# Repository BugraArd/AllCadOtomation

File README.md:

# AllCadOtomation — pcbqa

KiCad üzerinde çalışan bir **devre tasarımı otomasyonu ve kalite denetimi**
aracı. Saf Python'dur (çalışma zamanı bağımlılığı yok) ve KiCad'in kendi
Python'uyla çalışır.

Yaptıkları:

- **Analiz:** `.kicad_sch` + `.kicad_pcb` okunur, kaynaklı kural kütüphanesiyle
  (IPC-2221B, üretici uygulama notları) denetlenir ve skorlanır.
- **Devre grafı:** her parçanın pinleri, devredeki rolü, güç/gerilim sınırları,
  PCB karşılığı ve **eksik bilgileri** tek modelde toplanır.
- **Üç seviyeli doğrulama:**
  1. KiCad ERC / DRC / şematik paritesi
  2. parçaya ve amaca bağlı mühendislik kuralları
  3. **ngspice** benzetimi (tolerans, sıcaklık, yaşlanma)
- **PCB:** önce yerleşim ve kısıtlar, sonra dal akımına göre iz genişliği.
  Kirchhoff çözümüyle her iz parçasının gerçek akımı, darboğazlar, vialar ve
  gerilim düşümü hesaplanır.
- **Üretken tasarım:** niyet YAML'ından şematik + kart üretimi, otomatik
  yerleştirme, varyant keşfi (önce STM32).
- **KiCad'e bağlanma:** dosya, `pcbnew` (SWIG) ya da IPC. Açık PCB'de canlı
  düzenleme tek Ctrl+Z ile geri alınabilir.
- **ML veri hattı:** doğrulama ve yerleştirme sonuçları veri kümesine yazılır.

## Gereksinimler

| | Sürüm |
|---|---|
| KiCad | **10.0.4** (kicad-cli, sembol/footprint kütüphaneleri, `ngspice.dll`) |
| KiCad'in Python'u | 3.11.5 — dağıtımda bunu kullanır (`pcbqa.cmd`) |
| Geliştirme | Python 3.13 + `pcbqa/.venv` (`pyyaml`, `kicad-python`) |
| Benzetim | ngspice-46 (KiCad ile gelir; ek kurulum gerekmez) |
| İsteğe bağlı | KiCad nightly 10.99 (yalnızca canlı şematik için, `pcbqa/.runtime/`) |

## Hızlı başlangıç

```bat
cd pcbqa
pcbqa tani                                     :: ortam denetimi
pcbqa analiz samples\pic_programmer            :: kalite raporu
pcbqa devre  <proje>                           :: devre grafı ve eksikler
pcbqa dogrula <proje> --kosullar k.yaml        :: ERC/DRC + mühendislik + ngspice + PCB + 9 kontrol
pcbqa kontrol <proje> --kosullar k.yaml        :: hepsi tek koşuda: kalite skoru + doğrulama (ERC/DRC bir kez)
pcbqa uret --intent samples\niyetler\g031-asgari.yaml --out cikti\g031
pcbqa arayuz                                   :: masaüstü arayüzü (Yap, Devre, Kontrol, Düzelt, Deney, Üret, Canlı)
```

Kurulum ayrıntısı: `docs/KURULUM.md`. Tüm komutlar: `pcbqa --help`.

## Klasör yapısı

```
Kicad/
├─ pcbqa/                  uygulama
│  ├─ pcbqa/               Python paketi
│  │  ├─ app.py            tek giriş noktası (alt komutlar)
│  │  ├─ devre/            ortak devre modeli (graf, parça bilgisi, roller, koşullar)
│  │  ├─ dogrulama/        seviye 1-2-3 + dokuz kontrol
│  │  ├─ spice/            ngspice entegrasyonu
│  │  ├─ pcb_akim.py       dal akımı ve yönlendirme girdisi
│  │  ├─ rules.py, ipc2221.py, thermal.py, circuit.py   kural motoru ve hesaplar
│  │  ├─ placement/        yerleştiriciler (auto = üretim)
│  │  ├─ sch_*.py, pcb_sync.py   şematik/kart yazma (netlist kalkanıyla)
│  │  ├─ intent.py, generate.py, explore.py, templates/   üretken tasarım
│  │  ├─ canli*.py, ipc*.py, swig_apply.py   KiCad bağlantısı
│  │  ├─ data/parcalar/    kaynaklı parça bilgi kütüphanesi
│  │  └─ ml/               veri kümesi ve modeller
│  ├─ tests/               1035 unittest
│  └─ samples/             örnek projeler ve niyetler
├─ docs/                   TÜM belgeler: HANDOFF, KURULUM, tasarım kuralları,
│                          yol haritası, devre modeli, hafiza/ (Beads'ten üretilir), paketler/
├─ graphify-out/           bilgi grafiği
├─ .beads/                 iş takibi ve kalıcı hafıza (Beads)
├─ AGENTS.md               yapay zekâ ajanları için tek dosya (kurallar + yapı + hafıza)
└─ CLAUDE.md               AGENTS.md'yi içe aktarır
```

Özelliklerin tam haritası (hangi komut hangi modülde, ne yapar) `AGENTS.md`
bölüm 4'te.

## Testler

```bat
cd pcbqa
.venv\Scripts\python.exe -m unittest discover -s tests          :: 1035 test, ~5 dk
.venv\Scripts\python.exe -m unittest discover -s tests -p "test_spice.py"
```

Son koşu 2026-10-01'de yapıldı: 1035 test, hepsi geçti. Dosya bazında liste
`AGENTS.md` bölüm 6'da.

## Belgeler

| Belge | İçerik |
|---|---|
| `pcbqa/README.md` | Uygulamanın ayrıntılı kullanımı |
| `docs/HAFIZA-HARITASI.md` | Tüm hafıza, ayar ve belge dosyaları: nerede, neden orada |
| `docs/KURULUM.md` | Kurulum, kısayol, canlı mod |
| `docs/HANDOFF.md` | Tam geliştirme bağlamı ve ölçülmüş kararlar |
| `docs/devre-modeli-ve-dogrulama.md` | Devre grafı, 3 seviyeli doğrulama, PCB dal akımı |
| `docs/tasarim-kurallari/` | Kural eşiklerinin kaynakları |
| `docs/yol-haritasi-skorlama.md` | Yol haritası |
| `docs/duzeltme-siralama.md` | ML ilk deneyi: düzeltme adayı sıralama, sonuçlar ve eksikler |

## Proje hafızası

İşler ve kalıcı kararlar **Beads**'te tutulur (`bd ready`, `bd recall <anahtar>`).
Kod ve belge ilişkileri **graphify** bilgi grafiğinde sorgulanır
(`graphify explain "<kavram>"`). Serena kullanılmaz.

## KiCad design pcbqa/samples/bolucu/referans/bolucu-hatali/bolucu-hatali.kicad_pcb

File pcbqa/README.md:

# pcbqa — KiCad tasarım kalite analizi ve otomatik yerleştirme

KiCad projelerini **salt-okunur** analiz eden bir araç. Tasarımınızda hiçbir
değişiklik yapmaz — sadece okur, ölçer ve rapor eder.

## Ne yapar?

KiCad şematiği ile PCB'yi ayrı ayrı bilir ama **ikisini birleştirmez**. ERC size
"bu pin bağlı değil" der; "bu decoupling kondansatörü 33 mm ötede" demez.
`pcbqa` tam olarak o boşluğu doldurur:

```
U2.VCC_14 için en yakın C1 33.3 mm uzakta (hedef <= 20 mm), net VCC
```

Üç kaynağı tek raporda birleştirir:

| Kaynak | Ne verir |
|---|---|
| `kicad-cli sch export netlist` | Hangi pin hangi nette, pin işlevleri ve tipleri |
| `.kicad_pcb` | Bileşenlerin ve pad'lerin fiziksel konumu, courtyard, kart sınırı |
| `kicad-cli sch erc` / `pcb drc` | KiCad'in kendi kontrolleri |

**Şematik zorunlu değil.** KiCad 9+ pad'lerde hem net adını hem pin tipini
sakladığı için kuralların neredeyse tamamı sadece `.kicad_pcb` ile çalışır.
Şematik varsa ek olarak pin işlev adları (`VCC_8`) ve net sınıfları gelir.

## Kurulum

Gereksinim: KiCad 9 veya üzeri (`kicad-cli` için) ve Python 3.10+.
IPC ile çalışan KiCad'e placement yazmak için ayrıca `kicad-python` kurulur.

```powershell
cd C:\Users\ardaa\OneDrive\Desktop\Kicad\pcbqa
python -m venv .venv
.\.venv\Scripts\python -m pip install -r requirements.txt
```

`kicad-cli` otomatik bulunur (PATH → `C:\Program Files\KiCad\*\bin`). Gerekirse:

```powershell
$env:PCBQA_KICAD_CLI = "C:\Program Files\KiCad\10.0\bin\kicad-cli.exe"
```

## Kullanım

```powershell
# Demo proje üzerinde
.\.venv\Scripts\python -m pcbqa samples\pic_programmer

# Kendi projeniz + kendi kurallarınız + JSON çıktı
.\.venv\Scripts\python -m pcbqa C:\yol\projem --rules rules.yaml --json rapor.json

# Bulguları kimlikleri ve kanıtlarıyla listele
pcbqa duzelt C:\yol\projem --liste

# Bir bulguyu doğrudan düzelt (planı yazar ve aynı koşumda uygular)
pcbqa duzelt C:\yol\projem --finding F-123456789abc

# İlk STM32G0 profilinden geçici KiCad projesi üret
pcbqa uret --intent samples\niyetler\g031-asgari.yaml --out C:\yol\g031-kart

# BOM'da yalnızca kaynağı doğrulanmış kalemleri üretime kabul et
pcbqa bom samples\bom\g031-asgari.yaml --fail-on-open
```

Ya da kısayol: `run.cmd samples\pic_programmer`

### Var olan sembolleri telleme (`bagla`)

```powershell
# Sayfaya baksın ve gerekçesiyle önersin (yazmaz)
.\.venv\Scripts\python -m pcbqa.connect samples\uc_parca\uc_parca.kicad_sch --oner

# Öneriyi çiz
.\.venv\Scripts\python -m pcbqa.connect samples\uc_parca\uc_parca.kicad_sch --oner --uygula

# Ya da hangi pinlerin aynı ağa gireceğini kendiniz söyleyin
.\.venv\Scripts\python -m pcbqa.connect <şematik> --ag "#PWR01.1 R1.1 C1.1" --uygula
```

`--oner` niyeti **yerleşimden** okur: iki boş pin birbirinin en yakın hizalı
komşusuysa ve aralarında engel yoksa bağlanır; güç sembolü bir rayın ortasına
dik iniyorsa oraya iner. Kanıtı olmayan hiçbir şey önerilmez ve **atlanan pin
adıyla söylenir**. Aynı sembolün kendi pinleri asla eşleşmez — o hizalama
sembolün geometrisinden gelir, kullanıcının yerleşiminden değil.

Yazdıktan sonra `kicad-cli` netlist'i hakemdir: istenen pinler gerçekten aynı
ağa girmediyse komut hata döner ve yedeğin yolunu söyler.

### Bulgu / düzeltme / doğrulama

`duzelt` komutu analiz bulgularına kararlı `Finding ID`, ölçüm ve kanıt özeti
verir. Paket 01'de yalnızca ölçülmüş decoupling mesafesi ihlalleri otomatik
düzeltme adayıdır.

`--finding` verilen komut **ayrı bir onay adımı beklemez** (kullanıcı talimatı,
2026-09-27): planı ekrana yazar ve aynı koşumda uygular. Güvenlik önizlemeden
değil yazma kapılarından gelir ve hepsi korunur — uygulama öncesi yedek alınır,
KiCad açıkken yazma reddedilir, sonrasında hedef bulgu ile netlist paritesi
tekrar kontrol edilir ve doğrulama başarısızsa dosya yedekten geri alınır.
Mevcut track/via/zone bulunan yönlendirilmiş kartlar otomatik dosya
uygulamasına hâlâ alınmaz.

### STM32G0 ilk profil

Paket 02’nin ilk dikey dilimi `mcu-stm32g031k8` şablonudur. Hedef parça
`STM32G031K8T6`, paket `LQFP-32_7x7mm_P0.8mm`’dir. Profil; güç, reset ve
temel SWD bağlantısını üretir. LQFP-32 varyantında USB ve HSE varsayılmaz;
PA14’ün SWCLK/BOOT0 çoklaması nedeniyle BOOT0 pulldown otomatik eklenmez.
Gerçek ürün BOM’u ve çevresel pin seçimi elektriksel gereksinim onayından
sonra kilitlenecektir.

### BOM kaynak kapısı

`pcbqa bom` fiyat veya stok uydurmaz. Her kalem `verified`, `needs_selection`,
`blocked` veya `synthetic` olarak görünür. `verified` kalemlerde MPN, üretici
ve kaynak zorunludur; `--fail-on-open` açık kalem varsa çıkış kodu `1` döndürür.

## Aşama 5: makine öğrenimi altyapısı

Aşama 3'ün dersi "yerleştirici, hakemin puanladığı şeyi optimize etmeli"ydi.
Aşama 5 sıradaki soruyu sorar: hakemin ölçümü **doğru ama pahalı** (60
bileşenli kartta 2 ms, `pic_programmer`da 6 ms, `jetson` gibi kartlarda çok
daha fazla — `auto`nun süre bütçesini aşmasının sebebi bu). Yerel arama saniyede
binlerce aday dener; bunların hangisinin denemeye değer olduğunu **öğrenilmiş
bir model** söyleyebilir mi?

```powershell
# 1) Gerçek hakemle etiketlenmiş veri topla
.\.venv\Scripts\python -m pcbqa.ml.collect --suite "C:\Program Files\KiCad\10.0\share\kicad\demos" `
    --board samples\bench_bad.kicad_pcb --rules pcbqa\default_rules.yaml `
    --out .work\moves.jsonl --budget 25

# 2) Modelleri eğit ve KARŞILAŞTIR (mean = taban çizgisi, identity'nin ML karşılığı)
.\.venv\Scripts\python -m pcbqa.ml.train .work\moves.jsonl --model all --target all --cv 5 `
    --out pcbqa\ml\models\move-v1.json

# 3) Öğrenilmiş sıralamayla yerleştir
.\.venv\Scripts\python -m pcbqa.harness --placer auto --placer learned --board samples\bench_bad.kicad_pcb
```

### Model karar vermez, sıra önerir

Bu ayrım altyapının tamamını belirledi. Model yalnızca aday hamleleri
**denenme sırasına** dizer; bir hamlenin kabul edilip edilmeyeceğine hâlâ
`ctx.evaluate` (gerçek hakem) karar verir. Sonuçları:

- Model iyi çalışırsa aynı bütçede daha çok iyileşme yakalanır.
- Model **tamamen yanılırsa** sonuç sadece biraz yavaşlar; skor düşemez.
- Bozuk/eski bir model dosyası aramayı durduramaz — sıralayıcı patlarsa
  arama kendi sırasıyla devam eder.

Testlerde bu bilerek zorlanıyor: kasten **en kötü hamleyi başa alan** bir
sıralayıcıyla ve her çağrıda istisna fırlatan bir sıralayıcıyla `polish`
koşturuluyor; ikisinde de sonuç başlangıçtan kötü çıkmıyor.

### Ölçülen şey: kaç değerlendirmede ilk iyileşmeyi buluyoruz

R² değil. Yerel arama ilk iyileştiren hamleyi kabul ettiği için asıl soru
"skoru artıran hamleye kaçıncı denemede ulaşıldığı". Taban, cilanın **bugün**
kullandığı sıra. 21 karttan toplanan 49.699 örnekte, kart bazlı 5 katlı çapraz
doğrulama:

| model | hedef | ikili doğruluk | skor hızlanması |
|---|---|---|---|
| mean (taban) | — | 0.500 | 1.00x |
| ridge | sign | **0.714** | **1.56x** |
| gbt | score | 0.581 | 1.53x |
| ridge | score | 0.691 | 1.51x |
| gbt | value | 0.698 | 1.36x |
| ridge | value | 0.695 | 1.34x |

Yani öğrenilecek gerçek bir sinyal var: model, skoru artıran hamleyi ortalama
2.8 yerine ~1.4 denemede buluyor.

### Uçtan uca sonuç: `learned` şu an `auto`yu geçmiyor

Dürüst tablo şu: sıralama kazancı yerleştirme **kalitesine** yansımıyor.
Modelin hiç görmediği dört kartta (eğitim kümesinden çıkarılarak), 5 sn bütçe:

| kart | önce | `auto` | `learned` |
|---|---|---|---|
| pic_programmer | 45 | 94 | 94 |
| complex_hierarchy | 54 | 94 | 94 |
| sonde xilinx | 73 | 100 | 100 |
| interf_u | 5 | 12–14 | 12–15 |
| jetson (1125 bileşen, 60 sn) | 93 | 93.3 | 93.3 |

`interf_u` satırındaki oynama üç tekrarda `auto` için de aynı aralıkta çıkıyor
— duvar saati bütçesinden gelen gürültü, model etkisi değil. Sebep basit:
bu bütçelerde `auto` zaten doyuma ulaşıyor, sıralamayı hızlandırmak
ulaşılabilir tavanı yükseltmiyor. `learned` bu yüzden `force`/`anneal` gibi bir
**araştırma yerleştiricisi** olarak duruyor; üretim yerleştiricisi hâlâ `auto`.

### Yol boyunca bulunan iki gerçek problem

**1. Etiket seçimi model seçiminden daha önemli.** İlk model `sign` hedefiyle
(“hakemi mutlu eder mi”) eğitildi ve `complex_hierarchy`yi 94 → 81 **düşürdü**
— üstelik HPWL'i iyileştirerek (1680 → 1594). Sebep veri kümesinde görünüyor:
etiketi pozitif olan hamlelerin **%81'i skoru hiç değiştirmiyor**, yalnızca
teli birkaç mm kısaltıyor. Model bunları öğrenip cilayı mikro HPWL
kazançlarına yönlendirdi, hakemin saydığı hatalar açık kaldı. Kural: modele
neyi sıralamasını istiyorsak etiket **tam olarak o** olmalı (`--target score`).

**2. Her sıra bilgisiz değildir.** Onarım aşamasında hamleler zaten anlamlı bir
sırada üretiliyor: yarıçap artan, yani "en küçük yer değiştirme önce". Bu
muhafazakâr sıra komşu kısıtları bozmadığı için değerlidir; modelin "tek başına
en çok iyileştiren" hamlesi ise büyük sıçramalar seçip başka bulguları
açıyordu. Sıralayıcı bu yüzden **yalnızca ince ayar aşamasında** devreye
giriyor — orada sıra bugün zaten `rng.shuffle` ile rastgele, yani kaybedilecek
bilgi yok. Bu kısıtlamadan sonra dört model varyantının hiçbiri gerileme
yapmadı.

### Öznitelikler neden yerel

75 öznitelik var (şema v3) ve hepsi tek bir bileşenin **kendi netleri ve yakın
komşularıyla** hesaplanıyor; maliyet kartın büyüklüğüne değil bileşenin
derecesine bağlı. Ölçüldü:

| kart | bileşen | öznitelik | tam değerlendirme | oran |
|---|---|---|---|---|
| bench_bad | 18 | 32 µs | 2.09 ms | 65x |
| pic_programmer | 63 | 72 µs (v1) · 134 µs (v3) | 6.12 ms | 85x · 45x |

Şema v3 bulgunun **kendisini** de taşıyor: kural tipi, `(ölçülen − limit)/limit`
boşluğu ve — `proximity` için — hamleden sonraki ölçümün **birebir yeniden
hesabı**. `proximity` pin-pin mesafesi ölçtüğü için bileşen merkezi yaklaşımı
tam da kuralın karar verdiği eşiğin çevresinde yanılıyordu (SOIC-20'de bir pin
merkeze 5 mm uzakta olabilir). Ayrıntı: HANDOFF §14.

Yerel hesabın sessizce yanlış olmaması kritik — model o zaman sağlam veriyle
eğitildiğini sanır. Bu yüzden `d_hpwl` özniteliği testlerde **tam yeniden
hesaplamayla** karşılaştırılıyor.

### Bağımlılık yok

`numpy`/`scikit-learn` eklenmedi. Ridge regresyon (normal denklemler +
Cholesky) ve gradyan artırmalı ağaçlar (histogram tabanlı) saf Python;
problem boyutu (~50 öznitelik, ~50 bin satır) bunun için fazlasıyla küçük ve
proje `sexpr.py`den beri bağımlılıksız kalmayı tercih ediyor. Modeller
**JSON** olarak saklanıyor: git diff'i okunabilir, Python sürümleri arasında
taşınabilir, ve içinde çalıştırılabilir kod olmadığı için başkasından gelen bir
model dosyasını açmak güvenlik sorunu değil.

## Aşama 4a/4b: şematik okuma ve netlist kalkanı

KiCad 10'da IPC API'si yalnızca PCB editöründe var. Ama şematiği **okumak**
için IPC'ye gerek yok: `.kicad_sch` da s-expression. `pcbqa.schematic` onu
doğrudan okur — hiyerarşik alt sayfalar dahil.

```python
from pcbqa.schematic import read_schematic

sch = read_schematic("proje/proje.kicad_sch")   # alt sayfalara kendi iner
sch.stats()          # {'dosya': 2, 'sayfa': 2, 'sembol': 124, ...}
r1 = sch.by_ref("R1")
r1.pins              # sayfa koordinatına çözülmüş pinler
r1.bbox              # gövde sınır kutusu
```

Analiz raporuna `SEMATIK` bölümü olarak da yansır (`python -m pcbqa <proje>`)
ve dört yapısal kontrol ekler: eksik alt sayfa dosyası, ızgara dışı sembol,
footprint'i atanmamış bileşen, gövdeleri çakışan semboller.

### Pin konumu: deneysel olarak doğrulanmış dönüşüm

Kütüphane sembolünde Y **yukarı**, sayfada Y **aşağı** bakar; sembol ayrıca
döndürülmüş ve aynalanmış olabilir. Doğru dönüşüm tahminle değil, KiCad'in 19
demo projesinin tamamında ölçülerek seçildi:

| | örtüşme |
|---|---|
| `(px·cos − py·sin, −px·sin − py·cos)` | **%93.5** |
| rakip hipotez | %37.8 |
| ayna **rotasyondan sonra** | **%94.9** |
| ayna rotasyondan önce | %27.0 |

Okuyucu 19 projede, **17.088 pin** üzerinde doğrulandı: pinlerin **%98.7'si**
bir çapaya oturuyor, projelerin çoğunda %100, bozuk parantez 0.

> Çapa yalnızca tel ucu değildir. Bir pin junction'a, no-connect'e, etikete
> veya **doğrudan başka bir sembolün pinine** de değebilir — güç sembolleri
> (GND, VCC) çoğu zaman telsiz, doğrudan IC pinine yapışır. Dar bir ölçüt
> bunları "kaçan pin" sanar.

### Netlist değişmezliği kalkanı

Şematikte bağlantı **geometriktir**: tel ucu pine değiyorsa bağlıdır. PCB'de
durum farklı — orada net, pad'in içinde ismiyle yazılıdır. Sonuç: bir sembolü
şematikte kaydırmak bağlantıyı **sessizce** koparır.

Ölçüldü: `pic_programmer` üzerinde R1 kaydırıldığında pin 2 koptu ve netlist'te
`unconnected-(R1-Pad2)` olarak belirdi. Hiçbir hata, hiçbir uyarı. **Tek ızgara
adımı (1.27 mm) bile yetiyor.**

```python
from pcbqa.sch_verify import verify_unchanged

diff = verify_unchanged(onceki_sch, sonraki_sch)
if not diff.ok:
    print(diff.describe())    # "BAGLANTI DEGISTI: 7 pin baska aga tasindi"
    for satir in diff.details():
        print(satir)
```

Doğru değişmez, ham XML değil **pinlerin ağlara bölünüşüdür**. Net kodları her
ihracatta yeniden numaralanır ve otomatik net adları (`Net-(R1-Pad1)`)
konuma göre değişir; bunlar gerçek bağlantı değişikliği değildir. Bölünme aynı
kaldığı sürece devre elektriksel olarak aynıdır.

Bu kalkan, şematiğe yazma (Aşama 4c/4d) için ön koşuldur: yazma öncesi/sonrası
karşılaştırılır, `ok=False` ise yazma reddedilir.

## Aşama 4e: şematik yerleştirme kalitesi

Aşama 3'te PCB için kurulan mimari şematiğe olduğu gibi taşındı: yerleştirici
vekil bir maliyet uydurmaz, **hakemin gerçek ölçütünü** optimize eder ve sonuç
hiçbir zaman başlangıçtan kötü olamaz. `refine.polish` değiştirilmeden
kullanılır; değişen tek şey değerlendiricidir.

```powershell
# Bir sayfayı iyileştir (dry-run), sonra uygula
.\.venv\Scripts\python -m pcbqa.sch_apply --sch proje\proje.kicad_sch --budget 20
.\.venv\Scripts\python -m pcbqa.sch_apply --sch proje\proje.kicad_sch --budget 20 --apply

# Alt sayfa
.\.venv\Scripts\python -m pcbqa.sch_apply --sch proje\proje.kicad_sch --sheet /guc --apply
```

### İki hızlı, bir yavaş ölçüt

Kalkan her çağrıda `kicad-cli` çalıştırır (2-4 sn); yerel arama binlerce aday
dener. Bu yüzden ölçüt ikiye ayrıldı:

| | ne zaman | ne kadar sürer |
|---|---|---|
| Geometrik ölçüt (bellek-içi) | her adayda | **~0.4 ms** → 20 sn'de ~47.000 deneme |
| Netlist kalkanı | yalnızca yazmadan önce, **bir kez** | 2-4 sn |

Geometrik ölçüt bağlantı riskini de taşır: taşınan bir pin **kendisine ait
olmayan** bir çapaya (başka bir telin ucu, başka bir sembolün pini) oturursa
iki net birleşir. Bu, kalkanın yakaladığı hatanın ucuz vekili olduğu için arama
zaten oraya gitmez; kalkan son söz olarak kalır.

Ölçülen: `pic_programmer` kök sayfası 985.5 → 976.6 mm, skor 100'de sabit,
0 hata. Daha dağınık sayfalarda kazanç çok daha büyük (`video/RAMS` %21,
`vme-wren` kök sayfası %17).

### Bus içeren sayfalar: varsayılan olarak kapalı

Ucuz ölçüt bus bağlantılarını modelleyemiyor. `vme-wren/vme_p1_p2` sayfasında
(137 bus, 262 bus girişi) optimizasyon "skor 100, 0 hata, tel %60 kısaldı"
dedi; gerçek kalkan **257 pinin ağ değiştirdiğini** gösterdi ve yazma
reddedildi. Sistem güvenliydi ama ölçüm yanıltıcıydı.

Bu yüzden bus içeren sayfalarda optimizasyon kapalıdır. `allow_buses=True`
ile açılabilir — kalkan yine son söz olarak çalışır.

### Toplu uygulama

`sch_move` tek sembol taşır ve her çağrıda kalkanı çalıştırır — 30 sembol için
dakikalar. `sch_apply` tersini yapar: **tüm** taşımaları ağaç üzerinde uygular,
kalkanı **bir kez** çalıştırır, dosyayı **bir kez** yazar.

Bir nokta iki taşınan sembolün pinine denk gelip deltaları farklıysa, o noktayı
nereye götüreceğimiz belirsizdir — çatışma sayılır ve uygulama reddedilir.

### Sembol kimliği: UUID, referans değil

Çok birimli bir bileşenin (ör. 74LS125'in dört kapısı) her birimi ayrı bir
`symbol` düğümüdür ve **hepsi aynı referansı taşır**. Referansla anahtarlamak
dördünü tek girdiye çökertip "U2 ve U2 çakışıyor" gibi hayali bulgular
üretiyordu. Yerleştirme sözleşmesi bu yüzden `{sembol_uuid: (x, y)}`.

Yalnızca **öteleme**. Rotasyon ve ayna desteklenmiyor: pin konumları dönünce
tel uçları tek bir delta ile taşınamaz.

## Aşama 4c/4d: şematiğe yazma ve bağlantı koruyan taşıma

Bir sembolü kaydırıp bırakmak, pinlerine değen tel uçlarını yerinde bırakır ve
bağlantı **sessizce** kopar. `pcbqa.sch_move` sembolü taşırken ona tutunan her
şeyi birlikte taşır: tel uçları, junction ve no-connect işaretleri, etiketler,
sembolün kendi metin alanları.

```powershell
# Dry-run (varsayılan): ne olacağını söyler, dosyaya dokunmaz
.\.venv\Scripts\python -m pcbqa.sch_move --sch proje\proje.kicad_sch --ref R1 --dx 2.54 --dy 0

# Gerçekten yaz
.\.venv\Scripts\python -m pcbqa.sch_move --sch proje\proje.kicad_sch --ref R1 --dx 2.54 --dy 0 --apply
```

Çıktı:

```
  R1: (78.74, 43.18) -> (81.28, 43.18)  [tel ucu 2, junction 0, no-connect 0, etiket 0, property 5]
  KALKAN: baglanti degismedi
  UYGULANDI: 230,132 bayt yazildi
  yedek: pic_programmer.kicad_sch.pcbqa-bak
```

Hiyerarşide sembol hangi alt sayfadaysa **o dosya** düzenlenir; kök dosyaya
dokunulmaz.

### Üç katmanlı koruma

**1. Geometrik engel.** İki sembolün pini araya tel girmeden birbirine
değiyorsa (güç sembolleri çoğunlukla böyle bağlanır), uzatılacak tel yoktur ve
taşıma reddedilir:

```
  ENGEL: #PWR022 pini J1.5 ile dogrudan temas halinde (43.18, 101.6);
         arada tel yok, tasima baglantiyi koparir
```

**2. Netlist kalkanı.** Geometri her şeyi göremez. Taşınan bir tel ucu başka
bir netin üstüne oturabilir. Değişiklik önce bir kum havuzunda uygulanır ve
netlist karşılaştırılır:

```
  KALKAN: BAGLANTI DEGISTI: 15 pin baska aga tasindi
    J1.3: '/VPP_ON' (3 pin) -> 'VCC' (15 pin)
  tasima yapilmadi - baglanti bozulurdu
```

Bu örnek gerçek: `--apply` verilmiş olmasına rağmen dosyaya dokunulmadı.

**3. Atomik yazma.** IPC şematikte çalışmadığı için "editöre uygula, undo ile
geri al" seçeneği yok — yazma doğrudan dosyaya. Bu yüzden:

- geçici dosya **aynı dizine** yazılır → `fsync` → `os.replace` (Windows'ta da
  atomik; ayrı birimler arasında atomiklik garanti edilmez, o yüzden aynı dizin)
- yazmadan önce **yedek** alınır
- proje KiCad'de açıksa (`~<proje>.kicad_pro.lck`) yazma **reddedilir** —
  Eeschema dosyayı bellekte tutar, kullanıcı kaydederse değişikliğimiz kaybolur
- **UUID'ler asla yeniden üretilmez**; KiCad sembol örneklerini ve netlist
  yollarını onlarla izler

### Bayraklar

| Bayrak | Açıklama |
|---|---|
| `--apply` | Gerçekten yaz (varsayılan dry-run) |
| `--sheet` | Sembol birden fazla sayfadaysa sayfa yolu |
| `--no-snap` | 1.27 mm ızgaraya oturtma |
| `--no-verify` | Netlist kalkanını atla (**önerilmez**) |
| `--no-backup` | Yedek alma |
| `--force` | Engelleri ve kalkan reddini yok say |
| `--allow-open-project` | KiCad açıkken de yaz |

Izgaraya oturtma kaydırma miktarını değiştirir; tel uçları **aynı** miktarda
kaydırılır, yoksa pinden kopar.

Çıkış kodları: `0` başarılı · `1` engel/kalkan reddi · `2` araç hatası.

## Aşama 3: otomatik yerleştirme (`auto`)

`auto` üretim yerleştiricisidir. Üç katmandan oluşur:

1. **Kaba yerleşim** — `cluster` ile sıfırdan bir aday üretilir.
2. **Cila** — `refine.polish` hakemin **gerçek puanını** optimize eder.
   Hamleler doğrudan bulgulardan üretilir: "C1, U2.14'ten 33 mm uzakta"
   bulgusu, C1'i U2 çevresinde limitin içindeki halkalara taşımayı dener ve
   yalnızca ölçüm iyileşirse kabul eder.
3. **Gerileme tabanı** — kartın **mevcut hali** de bir aday olarak yarışır.

3. madde tasarım gereğidir: `auto` hiçbir kartı mevcut halinden kötü yapamaz.
Aynı koruma hakemde (`best_result`) ve IPC yazma yolunda (`select_winner`) da
vardır — skoru düşüren bir yerleştirme karta **hiçbir zaman** yazılmaz;
böyle bir durumda araç hata verip karta dokunmaz.

```powershell
# Tek kartta
.\.venv\Scripts\python -m pcbqa.harness --placer auto

# Yarışma: auto'yu diğer motorlarla karşılaştır
.\.venv\Scripts\python -m pcbqa.harness --all

# Regresyon paketi: bir klasördeki TÜM kartlarda koştur
.\.venv\Scripts\python -m pcbqa.harness --placer auto --budget 15 `
  --suite "C:\Program Files\KiCad\10.0\share\kicad\demos" `
  --rules pcbqa\default_rules.yaml
```

`--suite` herhangi bir kartta gerileme bulursa çıkış kodu `1` verir; tek kartta
iyi sonuç almak yetmez, sentetik tezgâha aşırı uyum tam olarak böyle yakalanır.

### Kendi yerleştiricinizi yazarken

`ctx.evaluate(placement)` hakemin gerçek ölçümünü döndürür (60 bileşenli kartta
~5 ms, yani 30 saniyelik bütçede binlerce deneme). Vekil bir maliyet
fonksiyonu uydurmak yerine bunu optimize edin — Aşama 3'te gerçek kartlardaki
gerilemelerin sebebi tam olarak bu ikisinin ayrışmasıydı.

## Aşama 2: IPC ile KiCad'e placement uygulama

Yerleştirme motorları `ref -> (x_mm, y_mm, rot_deg)` sözleşmesiyle ham placement
üretir. `pcbqa.ipc_apply` bu çıktıyı çalışan KiCad PCB Editor oturumuna yazar.
Varsayılan mod **dry-run**'dır; KiCad'e gerçek yazma için `--apply` açıkça
verilmelidir.

Önce KiCad'de aynı `.kicad_pcb` dosyasını açın ve Preferences > Plugins altında
IPC API'nin etkin olduğundan emin olun.

```powershell
# Yarışmayı çalıştır, kazananı seç, aktif KiCad kartına yazmadan doğrula
.\.venv\Scripts\python -m pcbqa.ipc_apply --board samples\bench_bad.kicad_pcb --no-color

# Kazanan placement'ı tek undo adımı olarak çalışan KiCad'e uygula
.\.venv\Scripts\python -m pcbqa.ipc_apply --board samples\bench_bad.kicad_pcb --apply --no-color

# Uygulamadan sonra KiCad kartını da kaydet
.\.venv\Scripts\python -m pcbqa.ipc_apply --board samples\bench_bad.kicad_pcb --apply --save

# Kazanan ham placement çıktısını kaydet; sonra aynı çıktıyı tekrar uygula
.\.venv\Scripts\python -m pcbqa.ipc_apply --write-placement-json .work\winner-placement.json
.\.venv\Scripts\python -m pcbqa.ipc_apply --placement-json .work\winner-placement.json --apply
```

Güvenlik davranışı:

- aktif KiCad kart adı `--board` dosya adıyla uyuşmazsa durur;
  bilinçli uygulama için `--allow-board-mismatch` gerekir.
- harness'in kilitli saydığı konnektör/montaj deliği referanslarını taşımaz.
- KiCad'de kilitli footprint'leri de taşımaz; gerekirse `--ignore-kicad-locks`.
- değişiklikleri `begin_commit` / `push_commit` ile tek undo adımı yapar.

### Seçenekler

| Bayrak | Açıklama |
|---|---|
| `--rules PATH` | YAML kural dosyası (varsayılan: cwd'deki `rules.yaml`, yoksa paketle gelen) |
| `--json PATH` | Raporu JSON olarak da yazar (CI / ileri işleme için) |
| `--no-kicad-checks` | ERC/DRC'yi atlar, sadece kendi kurallarımız çalışır (daha hızlı) |
| `--work-dir PATH` | Ara dosyaları (netlist.xml, erc.json, drc.json) saklar |
| `--fail-on` | `error` (varsayılan) / `warning` / `none` — çıkış kodunu belirler |
| `--kicad-cli PATH` | kicad-cli yolunu elle verir |

Çıkış kodları: `0` temiz · `1` eşiği aşan bulgu var · `2` araç hatası.

## Kurallar

Kurallar YAML ile tanımlanır, kod değiştirmek gerekmez. On dört tip var:

| Tip | Alan | Ne kontrol eder |
|---|---|---|
| `proximity` | güç / niyet | Bir pine, aynı nette belirli bir bileşen N mm'den yakın mı |
| `require_on_net` | niyet | Ada uyan her nette belirli türde bir bileşen var mı |
| `same_net` | niyet | Belirtilen pinler aynı nette mi |
| `net_length` | sinyal | Netin tahmini uzunluğu (HPWL) bütçeyi aşıyor mu |
| `length_match` | sinyal | Bir grup netin uzunluğu birbirine yakın mı (diferansiyel çift) |
| `keep_apart` | yerleşim | İki bileşen kümesi arasında **en az** N mm var mı |
| `courtyard_overlap` | üretim | Bileşenler çakışıyor mu, aralarında montaj boşluğu var mı |
| `edge_clearance` | üretim | Bileşenler kart kenarından yeterince içeride mi |
| `trace_width` | bakır | İz genişliği akımı taşımaya yetiyor mu (IPC-2221B) |
| `via_current` | bakır | Netteki via'lar akımı taşıyabiliyor mu |
| `clearance_voltage` | bakır | İki net arası açıklık gerilim farkına yetiyor mu |
| `copper_area` | bakır | Bir netin toplam bakır alanı aralıkta mı (SW alanı, termal) |
| `component_value` | devre | Bileşen **değeri** hesaplanan aralıkta mı |
| `buck_layout` | alt-devre | Regülatör yerleşimi — bileşenleri **topolojiden** bulur |

`trace_width` / `via_current` / `clearance_voltage` **yalnızca yönlendirilmiş
kartlarda** çalışır; yerleştirme aşamasında (kartta bakır yokken) sessizce
atlanırlar.

### `buck_layout` — ad değil topoloji

Diğer kurallar bileşeni **net adından** bulur (`net: "^(FB|VFB)$"`). Gerçek
kartlarda bu yetmiyor: KiCad geri besleme netini `Net-(U2-FB{slash}VSET)` diye
otomatik adlandırıyor ve hiçbir desen tutmuyor. Ama IC'nin **pin adı** "FB/VSET"
olarak duruyor.

`pcbqa/subcircuit.py` regülatörü topolojiden bulur — imza: bir IC'nin SW pini +
o nette bir indüktör — ve rolleri çıkarır (CIN, COUT, indüktör, FB dirençleri).
`buck_layout` ROHM'un kontrol listesini bu rollere karşı çalıştırır.

Gerçek KiCad demo kartlarında ölçüldü:

| kart | ad desenli | topolojik |
|---|---|---|
| CM5_MINIMA_3 | 19 bulgu, skor 19.0 | **1 bulgu, 85.2** |
| One-Air-Max | 32 bulgu, skor 20.4 | **4 bulgu, 70.3** |
| jetson | — | **0 bulgu, 100.0** |

Bulgular parçayı adıyla söylüyor: *"U702 (buck): indüktör L701 SW pininden
4.32 mm uzakta (ROHM: <= 4 mm)"*.

`keep_apart`, `proximity`nin tersidir ve gerçek bir boşluğu kapatır: üretici
kurallarının şaşırtıcı bir kısmı "yaklaştır" değil **"uzaklaştır"** der —
FB izi → indüktör ≥ 10 mm (ROHM), I2C pull-up → sıcaklık sensörü ≥ 10 mm (TI).
Yalnızca mesafe küçültmeye çalışan bir yerleştirici bunları sessizce ihlal eder.

```yaml
rules:
  - id: decoupling-mesafe
    type: proximity
    severity: error
    pin:     { kind: ic, pintype: power_in }
    partner: { kind: capacitor }
    max_distance_mm: 10
    exclusive: true        # her kondansatör en fazla bir pine sayılır

  - id: veri-hatti-pullup
    type: require_on_net
    net: "(SDA|SCL)"
    partner: { kind: resistor }

  - id: guc-raylari-ortak
    type: same_net
    severity: error
    pins: ["U1.8", "U5.14", "U6.1"]

  - id: usb-cift
    type: length_match
    groups: [["USB_DP", "USB_DM"]]
    tolerance_mm: 3

  - id: courtyard-cakisma
    type: courtyard_overlap
    clearance_mm: 0.2

  - id: kart-kenari
    type: edge_clearance
    min_distance_mm: 2.0
    ignore_refs: ["^J", "^MH"]   # konnektörler kasten kenardadır

  - id: guc-izi-genisligi
    type: trace_width
    net: "^(VIN|VBUS|VOUT)$"
    current_a: 2.0
    delta_t_c: 10                # varsayılan 10 °C sıcaklık artışı
    copper_oz: 1.0
    method: ipc2221              # ya da mm_per_amp (ROHM'un 1 mm/A kuralı)

  - id: guc-via-sayisi
    type: via_current
    net: "^VBUS$"
    current_a: 2.0

  - id: gerilim-acikligi
    type: clearance_voltage
    class: B2                    # B1 iç / B2 dış kaplamasız / B4 kaplamalı
    voltages:
      "^HV_": 400
      "^VBUS$": 5

  - id: pullup-sensorden-uzak
    type: keep_apart
    a: { kind: resistor }
    b: { kind: ic, ref: "^TMP" }
    min_distance_mm: 10.0
```

### Hazır kural kütüphanesi ve `include`

`pcbqa/presets/` altında, üretici app-note'larından ve IPC/IEC standartlarından
toplanmış eşikleri taşıyan dört ön ayar var. Kendi kural dosyanızdan dahil edin:

```yaml
include:
  - presets/uretim.rules.yaml      # her tasarımda geçerli, uyarlama gerekmez
  - presets/buck.rules.yaml        # tasarımda buck converter varsa
rules:
  - id: kendi-kuralim
    ...
```

| Ön ayar | İçerik |
|---|---|
| `uretim.rules.yaml` | courtyard (IPC-7351B), kart kenarı, fab min. iz, gerilim açıklığı |
| `buck.rules.yaml` | CIN/SW/FB/COUT mesafeleri, güç izi genişliği, via sayısı |
| `lineer-koruma.rules.yaml` | LDO, motor sürücü, ESD/TVS, sensör |
| `yuksek-hiz.rules.yaml` | decoupling (λ/40), kristal, I2C, diferansiyel çiftler |

Yollar dahil eden dosyaya göre çözülür; dairesel `include` ve tekrar eden kural
`id`'si hata verir. `uretim` ön ayarı devre tipinden bağımsızdır ve sağlam bir
gerçek kartta sıfır bulgu üretir (testle korunuyor).

Eşiklerin **hepsinin kaynağı yazılı**, kaynağı olmayanlar "mühendislik seçimi"
diye etiketli. Ayrıntı, çelişkiler ve ölçülemeyenler:
[docs/tasarim-kurallari/](../docs/tasarim-kurallari/README.md).

### `exclusive` neden önemli?

`proximity` kuralında `exclusive: false` (varsayılan) iken 3V3 gibi geniş bir
rayda **tek bir kondansatör bütün güç pinlerini "tatmin eder"** — eksik
decoupling görünmez olur. `exclusive: true` ile her kondansatör en fazla bir
pine sayılır (en yakından başlayarak eşleme yapılır), yani "her güç pininin
kendi kondansatörü olmalı" beklentisi gerçekten test edilir.

Mevcut tasarımlarda çok bulgu üretebilir; kademeli geçiş için önce `false`
ile deneyin.

**Seçici alanları** (`pin` / `partner`):

- `ref` — referans üzerinde düzenli ifade (`"^U"`)
- `kind` — `ic`, `capacitor`, `resistor`, `inductor`, `diode`, `transistor`,
  `crystal`, `connector`, `switch`, `fuse`, `testpoint`, `other`
- `value` — değer üzerinde düzenli ifade (`"100n"`)
- `pintype` — KiCad pin tipi: `power_in`, `input`, `output`, `bidirectional`, `passive`…
- `function` — pin adı üzerinde düzenli ifade (`"V(CC|DD)"`)

`defaults.ignore_nets` ile toprak/güç netleri tüm kurallarda atlanır (poligon
döküm yapılan netlerde mesafe ölçümü anlamsızdır).

## HPWL nedir?

*Half-Perimeter Wire Length* — bir netin tüm pinlerini saran en küçük
dikdörtgenin genişlik + yükseklik toplamı. Yönlendirme yapılmadan önce gerçek
bakır uzunluğunu tahmin etmenin endüstri standardı yoludur: hızlı ve yeterince
doğru. **Aşama 3'teki otomatik yerleştirme motorunun küçülteceği ana büyüklük
budur.**

## Skor nasıl hesaplanır?

```
ceza  = Σ bulgu_cezası
skor  = 100 × e^(−ceza / bileşen_sayısı)
```

Bir bulgunun cezası, kuralı `weight` belirtmişse odur; belirtmemişse
severity'den türetilir — **hata 8, uyarı 2, bilgi 0**.

Ceza bileşen sayısına bölündüğü için 40 bileşenli bir kartla 400 bileşenli bir
kartın skorları karşılaştırılabilir. Üstel eğri sayesinde skor tam 0'a doymaz —
25 hatalı kart ile 60 hatalı kart hâlâ ayırt edilebilir.

### Kural bazlı ağırlık

```yaml
- id: sicak-dongu-alani
  type: keep_apart
  severity: error
  weight: 24.0        # bu kuralın her bulgusu 24 puan yer
```

**Neden gerekli:** severity tek başına yeterli değil. Ölçülmüş etkisi olan bir
kural (TI AN-2155'in sıcak döngü deneyi: 6 → 18 mm² alanda EMI marjı 1.6 dB
kayıp) ile kaynaksız bir mühendislik seçimi aynı 8 puanı yiyordu.

- `weight` **verilmezse** eski davranış birebir korunur; ağırlık kullanmayan
  kural dosyaları aynı skoru üretir.
- `weight: 0` → kural raporda görünür ama skoru etkilemez.
- Yüksek ağırlıklı bir **uyarı**, varsayılan bir **hatayı** geçebilir. Bu
  bilinçlidir: severity "ne kadar acil", ağırlık "ne kadar önemli" demektir.
- `info` bulguları **her zaman** sıfırdır, kuralın ağırlığı ne olursa olsun.
  Somut nedeni: `max_findings` sınırına takılan kural sentetik bir bilgi
  bulgusu üretir, `trace_width` de yönlendirilmemiş net için bilgi verir —
  ağırlık bunlara uygulansaydı ağırlığı 24 olan bir kural hiçbir ihlal olmadan
  24 puan yazdırırdı.

### Orantılı ceza

İhlalin *ne kadar* büyük olduğu da cezaya yansıyabilir:

```yaml
- id: guc-izi-genisligi
  type: trace_width
  weight: 12.0
  scale: true       # varsayılan false
  scale_max: 3.0    # çarpan tavanı, varsayılan 3.0
```

```
aşım   = |measured − limit| / |limit|
çarpan = min(1 + aşım, scale_max)
ceza   = weight × çarpan
```

Mutlak değer bilinçli: bazı kurallarda ihlal `measured > limit` (net uzunluğu),
bazılarında `measured < limit` (iz genişliği). Tek ifade ikisini de doğru ölçer.

Üç durumda ölçekleme **yapılmaz** (çarpan 1.0):

- kural `scale` istememiş,
- bulgu `measured`/`limit` taşımıyor — `require_on_net` ve `same_net` ikili
  kurallardır, "ne kadar ihlal" diye bir şey yoktur; `scale: true` verilse bile
  sessizce sabit ağırlığa düşer,
- `limit == 0` — `courtyard_overlap`'te `clearance_mm: 0.0` yaygındır.

**Tavan neden şart:** `via_current`'ta kapasite sıfıra yaklaşırsa oran patlar ve
tek bir bulgu bütün skoru yutar.

**Ölçüldü (2026-08-28):** Tezgah kartlarında ve `pic_programmer`da tüm kurallar
`scale: true` yapılıp `auto` yeniden koşuldu; **yerleştirmede gerileme yok**,
sonuçlar birebir aynı. Beklenen bir sonuç: ölçekleme *monotondur* — aynı bulgu
kümesi için skor karşılaştırmasının işaretini değiştirmez, yalnızca büyüklüğünü.
Sıralama ancak farklı bulgu kümeleri karşılaştırılırken (sayı ile büyüklük takas
edilirken) değişir.

Ağırlıkların kanıt gücüne göre nasıl seçileceği ve sıradaki adımlar:
[docs/yol-haritasi-skorlama.md](../docs/yol-haritasi-skorlama.md).

Bu skor bilinçli olarak geçicidir. Aşama 3'te otomatik yerleştirme motorunun
küçülteceği **maliyet fonksiyonuna** dönüşecek; o yüzden ürettiği ara değerler
(HPWL, mesafe ihlalleri) ölçülebilir tutuluyor.

## Sentetik test tezgâhı

Yerleştirme motorunu (Aşama 3) geliştirmek için **kötü** bir karta ihtiyaç var —
temiz bir kartta optimize edilecek bir şey yoktur. `pcbqa.synth` aynı devreden
iki kart üretir:

```powershell
.\.venv\Scripts\python -m pcbqa.synth --out samples
```

| Kart | Ne | Skor |
|---|---|---|
| `bench_good.kicad_pcb` | Makul yerleşim — **hedef** | 67 / 100 |
| `bench_bad.kicad_pcb` | Kasıtlı kusurlu yerleşim — motorun düzelteceği kart | 2 / 100 |

Devre küçük bir MCU kartı: regülatör + MCU + EEPROM + kristal + USB. Devrenin
"doğru cevabı" `synth.py` içinde tanımlı — hangi kondansatörün hangi IC'ye ait
olduğunu, hangi netlerin diferansiyel çift olduğunu kod belirliyor. Yani
kuralların gerçekten doğru şeyi yakalayıp yakalamadığı kanıtlanabiliyor.

`bench_bad`'e ekilen 7 kusurun tamamı **taşınabilir** bileşenlerde: 4 uzak
decoupling/yük kondansatörü, 2 courtyard çakışması, bozuk USB çift simetrisi.
Kilitli bileşenlere (J1/J2 konnektörleri) kusur ekilmez — yerleştirici onları
taşıyamayacağı için düzeltilemez bir ceza olur ve ulaşılabilir tavanı
düşürürdü. Bu yüzden J1/J2 iki kartta da aynı, yasal konumda durur.

`bench_good`'un 1 hatası kasıtlıdır: `nRESET` pull-up'ı yok. Bu bir **devre**
kusuru, yerleşim kusuru değil — her iki kartta da var ve yerleştirme motoru
bunu asla düzeltemez. Motorun işi `2 → 67` mesafesini kapatmak.

```powershell
.\.venv\Scripts\python -m pcbqa samples\bench_bad.kicad_pcb --rules samples\bench.rules.yaml --no-kicad-checks
```

`--no-kicad-checks` önemli: tezgâh kartlarında **yönlendirme (track) yok**,
sadece yerleşim var. KiCad'in DRC'si o yüzden her neti "bağlanmamış" sayıp
onlarca gürültülü ihlal üretir (65 hata). Yerleşim çalışmasında bizi
ilgilendiren pcbqa'nın kendi kurallarıdır.

## Mimari

```
pcbqa/
  sexpr.py         s-expression okuyucu (bağımlılıksız, hatalı dosyalara toleranslı)
  geom.py          poligon çakışması (içbükeyde de kesin), mesafe, dışbükey kabuk
  pcb.py           .kicad_pcb  -> bileşen/pad/courtyard konumları
  netlist.py       kicadxml veya doğrudan PCB -> net/pin bağlantıları
  model.py         ikisini birleştirir + ölçümler (HPWL, yoğunluk)
  rules.py         YAML kural motoru (7 kural tipi)
  kicadcli.py      kicad-cli sarmalayıcısı (netlist, ERC, DRC)
  ipc.py           kicad-python ile çalışan KiCad PCB Editor'e placement yazar (API sunucusu gerekir)
  swig_apply.py    KiCad'in kendi Python'undan pcbnew ile uygular (API GEREKMEZ)
  confload.py      YAML varsa YAML, yoksa yanındaki JSON kopyası
  bundle.py        çalışma zamanı JSON kopyalarını üretir/denetler
  ipc_apply.py     kazanan yerleştiriciyi seçip IPC uygulamasını koşturan CLI
  report.py        terminal raporu + skor
  synth.py         sentetik test kartı üreteci
  intent.py        niyet beyanı + şablon kütüphanesi -> inşa planı
  generate.py      plandan sıfırdan KiCad projesi (şematik + kart + yerleşim + skor)
  explore.py       aynı niyetten N varyant üretir, ölçer, en iyisini seçer
  ml/collect_design.py  varyant koşumlarını eğitim verisine çevirir (3c)
  harness.py       yerleştiricileri koşturur, puanlar, kazanan kartı yazabilir
  schematic.py     .kicad_sch okuyucu (hiyerarşik, pin/bbox geometrisi çözülmüş)
  sch_verify.py    netlist değişmezliği kalkanı
  sch_write.py     atomik yazma + açık-proje koruması + yedek
  sch_move.py      bağlantı koruyan sembol taşıma
  sch_place.py     şematik yerleştirme optimizasyonu
  sch_apply.py     toplu uygulama (tek doğrulama, tek yazma)
  __main__.py      komut satırı
  placement/
    base.py        DONMUŞ arayüz: Placer, PlacementContext, Evaluation
    refine.py      bulgu güdümlü cila — hakemin gerçek puanını optimize eder
    auto.py        ÜRETİM yerleştiricisi: kaba + cila + gerileme tabanı
    learned.py     auto + öğrenilmiş hamle sıralaması (Aşama 5)
    repertoire.py  geniş hamle repertuarı: takas / küme taşıma (Aşama 6, opt-in)
    cluster.py / force.py / anneal.py / codex.py   yarışan motorlar
    baseline.py    identity / random (hakem doğrulaması)
  ml/              Aşama 5 — makine öğrenimi altyapısı
    features.py    DONMUŞ öznitelik şeması: tasarım + aday hamle -> vektör
    collect.py     gerçek hakemle etiketlenmiş veri kümesi üretir
    dataset.py     JSONL depolama + KART BAZLI bölme
    metrics.py     regresyon + sıralama metrikleri
    model.py       model sözleşmesi, JSON kaydet/yükle, kayıt defteri
    linear.py      ridge regresyon (saf Python)
    trees.py       gradyan artırmalı ağaçlar (saf Python)
    train.py       eğitim/karşılaştırma komut satırı
    models/        eğitilmiş modeller (JSON)
```

`ml/` içinde de aynı katmanlama var: `features.py` ve `collect.py` PCB'yi bilir,
geri kalanı bilmez. Şematik tarafı (Aşama 4e) aynı çekirdeği kullanmak
istediğinde yalnızca yeni bir `features`/`collect` çifti yazmak yetecek.

`model.py` ve `rules.py` KiCad'i **hiç bilmez** — sadece kendi veri modelini
görürler. Bu ayrım bilinçli: Aşama 3'ün yerleştirme motoru da aynı modeli
kullanacak, ve KiCad 11 şematik API'sini getirdiğinde sadece yeni bir okuyucu
eklenecek.

## Neden Aşama 0/1'de IPC API (kicad-python) değil?

Aşama 0/1'in tamamı `kicad-cli` ile çalışır. Bunun sonucu:

- KiCad'in açık olması gerekmez → CI'da / komut satırında çalışır
- IPC bindings'in alpha olmasından ve Python sürüm desteği sorunlarından etkilenmez
- Yazma işlemi olmadığı için tasarımı bozma riski sıfır

Aşama 2'de IPC sadece seçilmiş placement çıktısını çalışan PCB Editor'e
uygulamak için kullanılır; analiz ve skor modeli hâlâ KiCad'den bağımsızdır.

## Dayanıklılık

KiCad 10.0.4 ile gelen `royalblue54L_feather` demosunun `.kicad_pcb` dosyasında
349 yerde bozuk s-expression var (`(curved_edges no)filter_ratio 0.9)` — açılış
parantezi eksik). Okuyucu bu tür bozukluklarda çökmez: hatalı parantezleri
atlar, kalan üst düzey düğümleri köke bağlar ve raporda uyarı gösterir. O
dosyada 71 bileşenin tamamı yine de okunabiliyor. Katı davranış isterseniz
`sexpr.parse(text, strict=True)`.

**Döndürülmüş bileşenler.** Kapladıkları alanı eksen-hizalı sınır kutusuyla
temsil etmek ciddi yanlış alarm üretir: stickhub demosunda `U1` -135° dönük,
gerçek courtyard'ı eğik bir dikdörtgen ama sınır kutusu çok daha büyük bir kare
— yakınındaki kondansatörler o karenin köşelerine düşüyor ve "çakışıyor" gibi
görünüyorlardı. Çakışma testleri artık gerçek poligon üzerinden yapılıyor ve bu yanlış
alarmlar ortadan kalktı.

Poligonlar **içbükey olabilir** ve öyle okunur: courtyard parçaları uç uca
zincirlenir. Dışbükey kabuğa çevirmek (ve ayırıcı eksen teoremi kullanmak)
L biçimli bir konnektörün *boşluğunu* dolu sayıyor, o boşlukta duran
kondansatörü "çakışıyor" gösteriyordu — `pic_programmer`da P3/C7'de ölçüldü.
Çakışma testi bu yüzden kenar kesişimi + içerme ile yapılır: her basit
poligonda kesin, dışbükeyde SAT ile aynı cevap.

**KiCad'in DRC'si her şeyi yakalamaz.** `courtyards_overlap` kontrolü proje
ayarlarından kapatılabiliyor — stickhub demosunda kapalı, o yüzden KiCad 0 ihlal
raporluyor. Aynı kartta gerçekten çakışan bileşenler var (örn. `J7` ve `J8`,
7 mm arayla yerleştirilmiş ama courtyard'ları 7.8 mm yüksek). pcbqa bu kontrolü
proje ayarlarından bağımsız yapar.

Doğrulama: KiCad'in 19 demo projesinin 17'sinde sorunsuz çalışıyor. Atlanan 2
tanesi zaten tam proje değil (PCB'si yok) ve temiz hata mesajı veriyorlar.

## Sınırlar

- Şematik **konumları** okunmuyor (KiCad 10'da IPC şematik desteği yok);
  şematikten sadece bağlantı bilgisi alınıyor.
- Courtyard poligonu **dışbükey kabuk** ile alınıyor. Dikdörtgen courtyard'lar
  için birebir doğru; nadir görülen içbükey (L/U şekilli) courtyard'larda
  güvenli tarafta kalır, yani fazladan bulgu üretebilir.
- Dairesel courtyard'larda alan bir miktar küçük çıkabilir (`fp_circle` için
  merkez + çevre noktası kullanılıyor).
- `length_match` HPWL üzerinden çalışır; gerçek uzunluk eşleme kontrolü değil,
  "bu iki net çok farklı yerlerde duruyor" ön uyarısıdır.
- Yoğunluk en yoğun **yüz** üzerinden hesaplanır (çift taraflı kartlarda iki
  yüzün alanını toplamak %100'ü aşan anlamsız sonuçlar verirdi).
- HPWL bir tahmindir; gerçek bakır uzunluğu değil. Yönlendirme öncesi
  karşılaştırma için tasarlanmıştır.
- **Geniş hamle repertuarı (`repertoire.py`) varsayılan olarak kapalı.**
  Takas/küme taşıma tel uzunluğunu iyi kısaltıyor (doymuş yerleşimde küme
  hamlelerinin %28'i hakemin sıralama anahtarını iyileştiriyor) ama kural
  bulgularını neredeyse hiç kapatmıyor (%0.3), yani skoru yükseltmiyor.
  Açmak için `ctx.allow_wide_moves = True`. Ayrıntılı ölçüm: HANDOFF §13.
- **Öğrenilmiş sıralayıcı (`learned`) uçtan uca henüz kazanç vermiyor.**
  Model sıralamayı ölçülebilir şekilde iyileştiriyor (çapraz doğrulamada
  1.56x) ama bu bütçelerde `auto` zaten doyuma ulaştığı için yerleştirme
  kalitesi değişmiyor. Üretim yerleştiricisi `auto`.

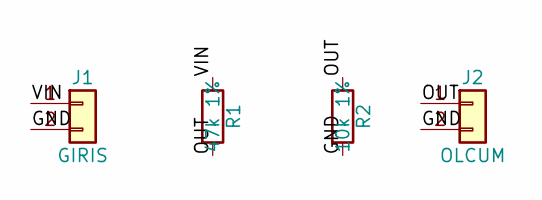
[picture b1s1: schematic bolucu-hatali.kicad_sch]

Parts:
J1: GIRIS; PinHeader_1x02_P2.54mm_Vertical
J2: OLCUM; PinHeader_1x02_P2.54mm_Vertical
R1: 47k 1%; R_0603_1608Metric
R2: 10k 1%; R_0603_1608Metric

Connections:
/GND: J1.2, J2.2, R2.2
/OUT: J2.1, R1.2, R2.1
/VIN: J1.1, R1.1

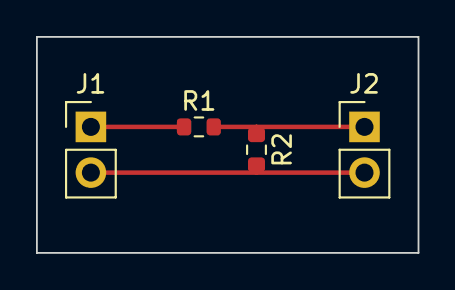
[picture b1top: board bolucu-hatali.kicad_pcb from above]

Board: 2 copper layers, 21.2 x 12.0 mm, 4 parts (0 on the bottom side), 3 nets.

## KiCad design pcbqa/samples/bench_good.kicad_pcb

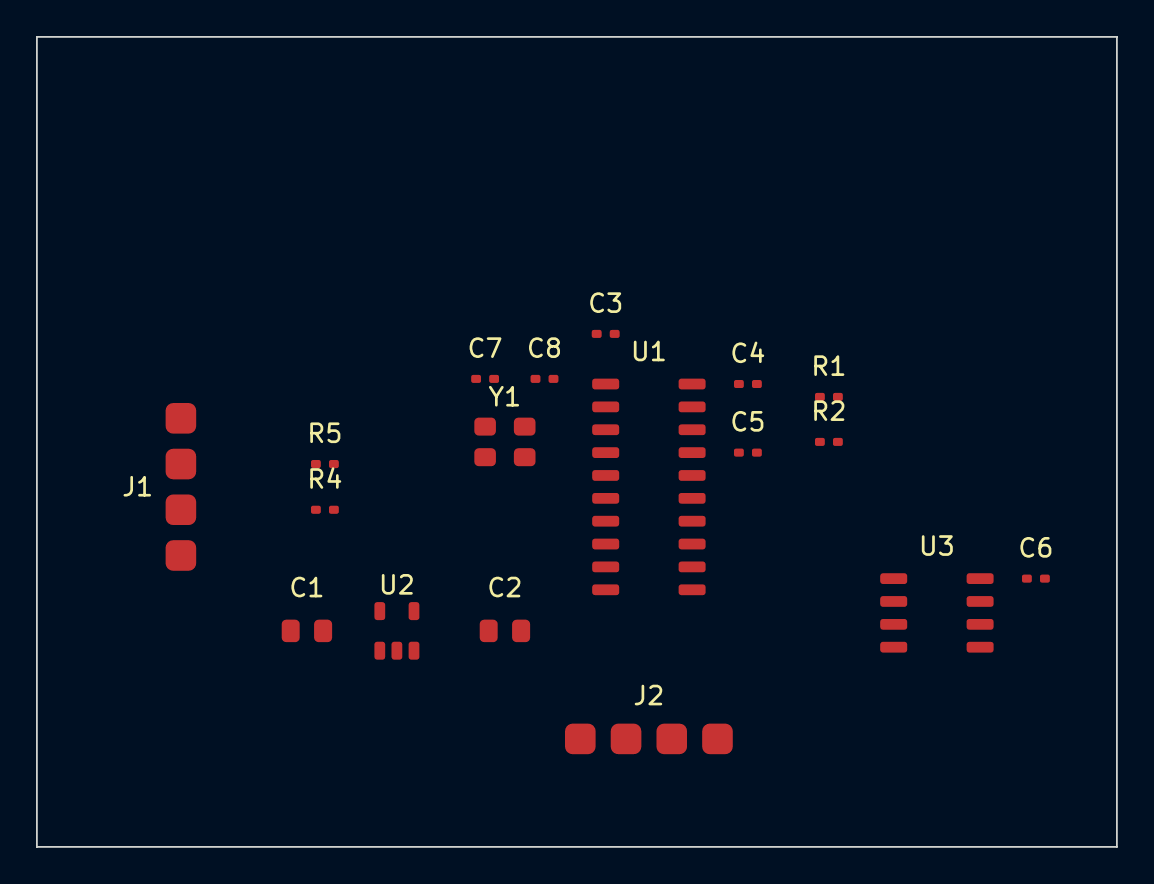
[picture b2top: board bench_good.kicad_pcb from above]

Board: 2 copper layers, 60.0 x 45.0 mm, 18 parts (0 on the bottom side), 15 nets, no tracks yet.

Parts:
C1, C2: 10uF; C_0805
C3, C4, C5, C6: 100nF; C_0402
C7, C8: 22pF; C_0402
J1: USB-C; PinHeader_1x04
J2: UART; PinHeader_1x04
R1, R2: 4k7; C_0402
R4, R5: 22R; C_0402
U1: MCU32; SOIC-20
U2: AP2112K-3.3; SOT-23-5
U3: 24C16; SOIC-8
Y1: 12MHz; Crystal_3225

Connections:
3V3: C2.1, C3.1, C4.1, C6.1, J2.1, R1.2, R2.2, U1.1, U1.20, U2.5, U3.8
AGND: C5.2, U1.18
AVDD: C5.1, U1.17
DM_MCU: R4.2, U1.11
DP_MCU: R5.2, U1.12
GND: C1.2, C2.2, C3.2, C4.2, C6.2, C7.2, C8.2, J1.4, J2.4, U1.2, U1.10, U2.2, U3.1, U3.2, U3.3, U3.4, U3.7, Y1.2, Y1.4
RX: J2.3, U1.9
SCL: R2.1, U1.7, U3.6
SDA: R1.1, U1.6, U3.5
TX: J2.2, U1.8
USB_DM: J1.2, R4.1
USB_DP: J1.3, R5.1
VBUS: C1.1, J1.1, U2.1, U2.3
XIN: C7.1, U1.3, Y1.1
XOUT: C8.1, U1.4, Y1.3
